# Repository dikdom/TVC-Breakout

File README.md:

# TVC-Breakout

## Magyar
Ez a repo olyan nyáklapok EagleCAD terveit tartalmazza, melyek a Videoton TVC számítógép programmodul és felső bővítő-helyeinek kivezetéseit teszik könnyen (könnyebben) elérhetővé hardverfejlesztők számára.
- _cart_ könyvtár tartalmazza a programmodul forrás file-jait, gerber file-t és a kapcsolási rajzot pdf-ben is.
- _exp_ könyvtár tartalmazza a felső bővítő forrás file-jait, gerber file-t és a kapcsolási rajzot pdf-ben is. Az r2-es változat az r1-hez képest annyival tud többet, hogy arra került egy 27C512 -es ROM foglalat is, kapcsolható A13-A15 vonalakkal. Az ellenállások 3# -ra lettek tervezve, hogy egyszerűbben lehessen bele LED -et tenni.
- _imgs_ könyvtár a már elkészült nyáklapokról tartalmaz fényképeket
- _lib_ könvytár a szükséges alkatrész-könyvtárakat tartalmazza
- OPCIONÁLIS: Az exp lap r2 -es változata tartalmazhat egy 64kB -os EEPROM -ot. Ha ebből csak a legfelső 8kB van használatban, akkor nem kell semmi mást csinálni a lapon. Amennyiben lapozás szükséges, az EEPROM az A13-A15 jeleit a lap kívülről kell megkapja (neked kell legenerálnod és az EX_A13, EX_A14, EX_A15 illetve az /EX_CE helyeken visszahozni a jobb alsó tüskesoron). Ilyenkor az A13, A14, A15 és /CE jumperek alját vágni kell és beállítani, hogy honnan érkezzen a címjel + /CE jel. A /CE jel alapból a TVC /EXPn jele. 
- OPCIONÁLIS: a jeleket vagy a kábelek beforrasztásával, vagy egy tüskesor beillesztésével és szalagkábellel lehet elvezetni.
-- Az exp lapon 3db 2x20 -as tüskesornak van hely amikhez 40 eres szalagkábelek kellenek. Ha megnézed, az egyik tüskesor kiválogatott jeleket tartalmaz. Tanulmányozd, mert lehet, h neked elég csak azokat a jeleket elhozni a lapról. Az alsó két headersor az összes TVC kivezetést tartalmazza.
-- A cart lapon 1db 2x17 -es tüskesornak van hely, amihez 34 eres szalagkábel kell.
- OPCIONÁLIS: Mindkét lap tartalmaz helyeket ú.n. polifuse-nak, azaz öngyógyító biztosítéknak a +5V -os és a +12V (csak exp) ágon. Jelölésük F1 (és F2 az exp lapon). Nem muszáj berakni, viszont védelmet jelent a TVCnek. Ha berakod, akkor ne felejtsd el elvágni alul a nyákon az átvezetést (ha már elvágtad, akkor be KELL rakni a biztosítékot)!
- OPCIONÁLIS: Mindkét lap tartalmaz LED-nek és ellenállásnak helyet, melyek visszajelzésként tudnak szolgálni a +5V és a +12V (csak exp lapon) ágaknak.
-- Az exp lapon 3mm -es LEDek és 5k1 és 12k értékű ellenállások kellenek
-- A cart lapon 5mm -es LED és egy 5k1 értékű ellenállás kell
-- Az értékek nem kőbevésett számok, ha azt akarod, hogy jobban világítson a LEDed, akkor rakj be kisebb ellenállást - de csak ésszel (tudd, hogy mit csinálsz)!
- FONTOS: a felső bővítő r1 és r2-es változata is le lett gyártva, működnek. A programmodulból gyártott r1 -es változatban a GND nem volt bekötve. Ez lett javítva az r2-ben, viszont abból még nem gyártattam, de más változtatás nem lett a nyáklapon, működnie kell. Az r1-es - hibás - válozatot nem is töltöttem fel, minek.

## English
This repository contains breakout board PCB plans for the Videoton TVC computer in EagleCAD. There are two type of TVC sockets I plan to provide help in this repo : 
- cartridge socket: This is the programmodule connector on the left side of the computer (cartridges uses this socket).
- expansion socket: There are 4 sockets on the top of the computer for IO board expansions (floppy and serial expansion cards use these connectors)

These PCBs is aiming to help new card builders to get easily all the signals from each of the connector. 
- _cart_ directory contains source files for the cartridge ('programmodul')
- _exp_ directory contains source files for the expansion ports.
- _imgs_ contains images about manufactured PCBs
- _lib_ directory contains the necessary library files
- OPTIONAL: both of the PCBs contain places for polifuse (marked as F1 and F2). If you place those you have to cut the wire on the back side of the PCB
- OPTIONAL: both of the PCBs contain places for LED and resistor. Those are just a visual signal to the hw developer if the TVC PSU provides the power (overheated TVC PSU needs some time to 'recover'). The resistor values are 5k1 for the 5V and 12k for the 12V, but those can be lowered if you want brighter LEDs (know what you are doing there!!). The LEDs are 3mm on the exp PCB and 5MM on the cart PCB.
- Both revisions of the exp PCB was manufactured and they works properly. The cart PCB r1 contained an error (GND pin was not connected on the header) so I fixed that but it wasn't manufactured yet. No other change was made, r1 otherwise works. 

# License: GNU GPL v3

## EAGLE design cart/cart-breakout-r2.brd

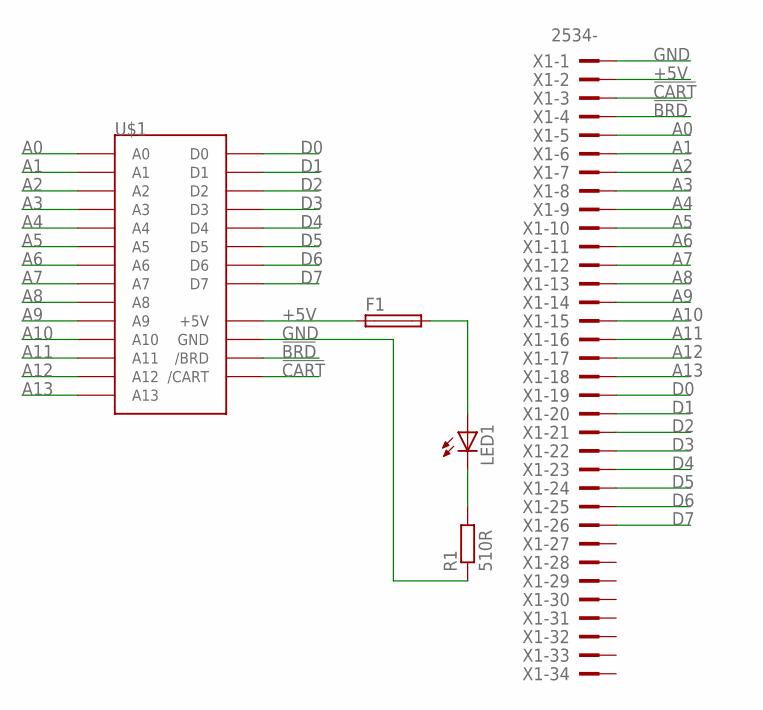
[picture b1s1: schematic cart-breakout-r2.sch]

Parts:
F1: TE5
LED1: LED5MM
R1: 510R; 0204/7
U$1: TVC-CART-EDGE+; TVC-CART-EDGE
X1: 2534-; PAK100/2500-34

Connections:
!BRD: U$1.BTM24 (/BRD), X1.4
!CART: U$1.BTM23 (/CART), X1.3
+5V: F1.1, F1.2, LED1.A, U$1.BTM10 (+5V), U$1.BTM11 (+5V), U$1.BTM12 (+5V), U$1.BTM13 (+5V), U$1.BTM14 (+5V), U$1.BTM15 (+5V), U$1.BTM16 (+5V), U$1.BTM17 (+5V), X1.2
A0: U$1.TOP25 (A0), X1.5
A1: U$1.TOP2 (A1), X1.6
A2: U$1.TOP24 (A2), X1.7
A3: U$1.TOP1 (A3), X1.8
A4: U$1.TOP21 (A4), X1.9
A5: U$1.TOP14 (A5), X1.10
A6: U$1.TOP18 (A6), X1.11
A7: U$1.TOP17 (A7), X1.12
A8: U$1.TOP15 (A8), X1.13
A9: U$1.TOP19 (A9), X1.14
A10: U$1.TOP22 (A10), X1.15
A11: U$1.TOP20 (A11), X1.16
A12: U$1.TOP16 (A12), X1.17
A13: U$1.TOP23 (A13), X1.18
D0: U$1.TOP4 (D0), X1.19
D1: U$1.TOP5 (D1), X1.20
D2: U$1.TOP6 (D2), X1.21
D3: U$1.TOP7 (D3), X1.22
D4: U$1.TOP8 (D4), X1.23
D5: U$1.TOP9 (D5), X1.24
D6: U$1.TOP10 (D6), X1.25
D7: U$1.TOP3 (D7), X1.26
GND: R1.1, U$1.BTM1 (GND), U$1.BTM2 (GND), U$1.BTM3 (GND), U$1.BTM4 (GND), U$1.BTM5 (GND), U$1.BTM6 (GND), U$1.BTM7 (GND), U$1.BTM8 (GND), X1.1
unnamed: LED1.K (C), R1.2

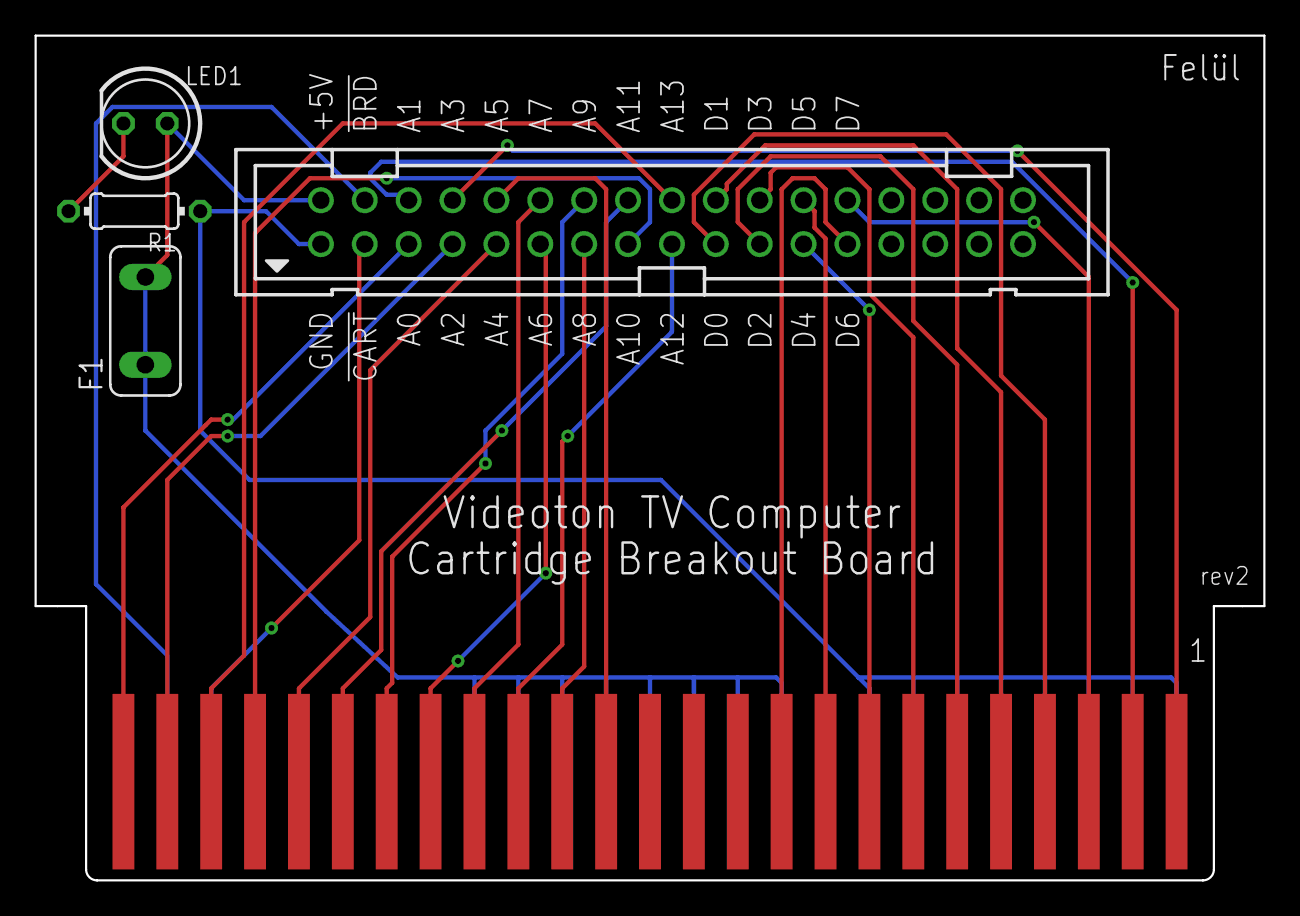
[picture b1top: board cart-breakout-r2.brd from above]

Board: 2 copper layers, 71.1 x 48.9 mm, 5 parts (0 on the bottom side), 27 nets.

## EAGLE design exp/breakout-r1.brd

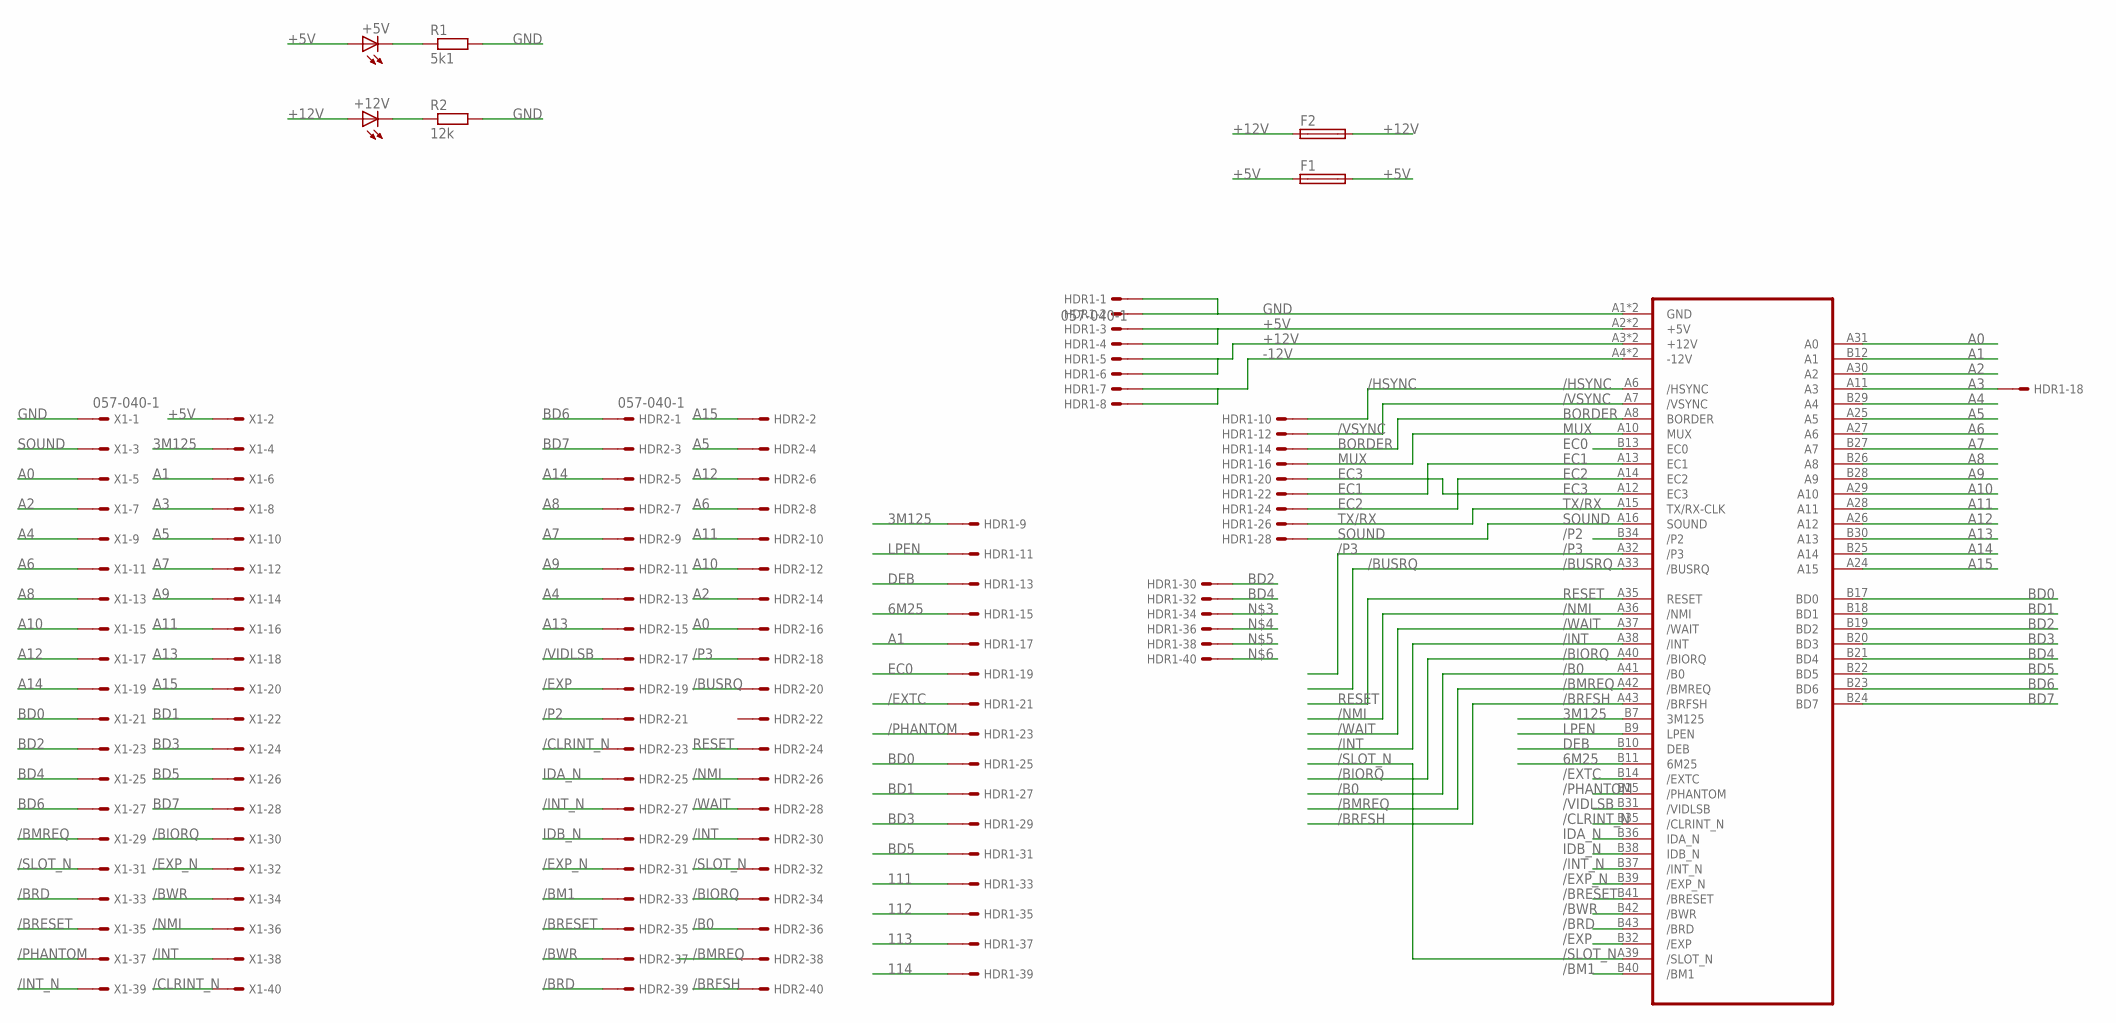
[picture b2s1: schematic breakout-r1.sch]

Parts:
+5V, +12V: LED3MM
F1, F2: TE5
HDR1, HDR2: 057-040-1
R1: 5k1; 0204/5
R2: 12k; 0204/5
U$1: TVC-EXP-HBA-COMMON; TVC-EXP-EDGE
X1: 057-040-1

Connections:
3M125: HDR1.9, U$1.B7 (3M125), X1.4
6M25: HDR1.15, U$1.B11 (6M25)
111: HDR1.33
112: HDR1.35
113: HDR1.37
114: HDR1.39
+5V: +5V.A, F1.1, F1.2, HDR1.3, HDR1.4, U$1.A2 (+5V), U$1.B2 (+5V), X1.2
+12V: +12V.A, F2.1, F2.2, HDR1.5, HDR1.6, U$1.A3 (+12V), U$1.B3 (+12V)
-12V: HDR1.7, HDR1.8, U$1.A4 (-12V), U$1.B4 (-12V)
/B0: HDR2.36, U$1.A41 (/B0)
/BIORQ: HDR2.34, U$1.A40 (/BIORQ), X1.30
/BM1: HDR2.33, U$1.B40 (/BM1)
/BMREQ: HDR2.38, U$1.A42 (/BMREQ), X1.29
/BRD: HDR2.39, U$1.B43 (/BRD), X1.33
/BRESET: HDR2.35, U$1.B41 (/BRESET), X1.35
/BRFSH: HDR2.40, U$1.A43 (/BRFSH)
/BUSRQ: HDR2.20, U$1.A33 (/BUSRQ)
/BWR: HDR2.37, U$1.B42 (/BWR), X1.34
/CLRINT_N: HDR2.23, U$1.B35 (/CLRINT_N), X1.40
/EXP: HDR2.19, U$1.B32 (/EXP)
/EXP_N: HDR2.31, U$1.B39 (/EXP_N), X1.32
/EXTC: HDR1.21, U$1.B14 (/EXTC)
/HSYNC: HDR1.10, U$1.A6 (/HSYNC)
/INT: HDR2.30, U$1.A38 (/INT), X1.38
/INT_N: HDR2.27, U$1.B37 (/INT_N), X1.39
/NMI: HDR2.26, U$1.A36 (/NMI), X1.36
/P2: HDR2.21, U$1.B34 (/P2)
/P3: HDR2.18, U$1.A32 (/P3)
/PHANTOM: HDR1.23, U$1.B15 (/PHANTOM), X1.37
/SLOT_N: HDR2.32, U$1.A39 (/SLOT_N), X1.31
/VIDLSB: HDR2.17, U$1.B31 (/VIDLSB)
/VSYNC: HDR1.12, U$1.A7 (/VSYNC)
/WAIT: HDR2.28, U$1.A37 (/WAIT)
A0: HDR2.16, U$1.A31 (A0), X1.5
A1: HDR1.17, U$1.B12 (A1), X1.6
A2: HDR2.14, U$1.A30 (A2), X1.7
A3: HDR1.18, U$1.A11 (A3), X1.8
A4: HDR2.13, U$1.B29 (A4), X1.9
A5: HDR2.4, U$1.A25 (A5), X1.10
A6: HDR2.8, U$1.A27 (A6), X1.11
A7: HDR2.9, U$1.B27 (A7), X1.12
A8: HDR2.7, U$1.B26 (A8), X1.13
A9: HDR2.11, U$1.B28 (A9), X1.14
A10: HDR2.12, U$1.A29 (A10), X1.15
A11: HDR2.10, U$1.A28 (A11), X1.16
A12: HDR2.6, U$1.A26 (A12), X1.17
A13: HDR2.15, U$1.B30 (A13), X1.18
A14: HDR2.5, U$1.B25 (A14), X1.19
A15: HDR2.2, U$1.A24 (A15), X1.20
BD0: HDR1.25, U$1.B17 (BD0), X1.21
BD1: HDR1.27, U$1.B18 (BD1), X1.22
BD2: HDR1.30, U$1.B19 (BD2), X1.23
BD3: HDR1.29, U$1.B20 (BD3), X1.24
BD4: HDR1.32, U$1.B21 (BD4), X1.25
BD5: HDR1.31, U$1.B22 (BD5), X1.26
BD6: HDR2.1, U$1.B23 (BD6), X1.27
BD7: HDR2.3, U$1.B24 (BD7), X1.28
BORDER: HDR1.14, U$1.A8 (BORDER)
DEB: HDR1.13, U$1.B10 (DEB)
EC0: HDR1.19, U$1.B13 (EC0)
EC1: HDR1.22, U$1.A13 (EC1)
EC2: HDR1.24, U$1.A14 (EC2)
EC3: HDR1.20, U$1.A12 (EC3)
GND: HDR1.1, HDR1.2, R1.2, R2.2, U$1.A1 (GND), U$1.B1 (GND), X1.1
IDA_N: HDR2.25, U$1.B36 (IDA_N)
IDB_N: HDR2.29, U$1.B38 (IDB_N)
LPEN: HDR1.11, U$1.B9 (LPEN)
MUX: HDR1.16, U$1.A10 (MUX)
unnamed: +5V.K (C), R1.1
unnamed: +12V.K (C), R2.1
RESET: HDR2.24, U$1.A35 (RESET)
SOUND: HDR1.28, U$1.A16 (SOUND), X1.3
TX/RX: HDR1.26, U$1.A15 (TX/RX-CLK)

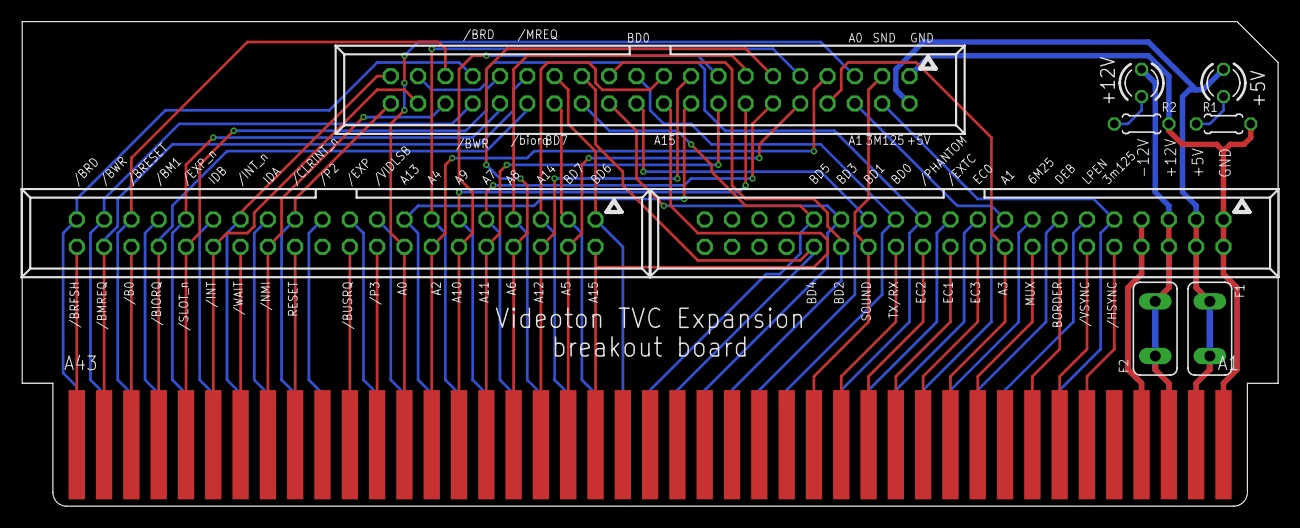
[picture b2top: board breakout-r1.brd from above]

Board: 2 copper layers, 116.8 x 45.0 mm, 10 parts (0 on the bottom side), 69 nets.

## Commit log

2021-04-10 Update README.md
    Indent fix
2021-04-10 W27C512 lib added for exp board
2021-04-10 Hungarian accents...
